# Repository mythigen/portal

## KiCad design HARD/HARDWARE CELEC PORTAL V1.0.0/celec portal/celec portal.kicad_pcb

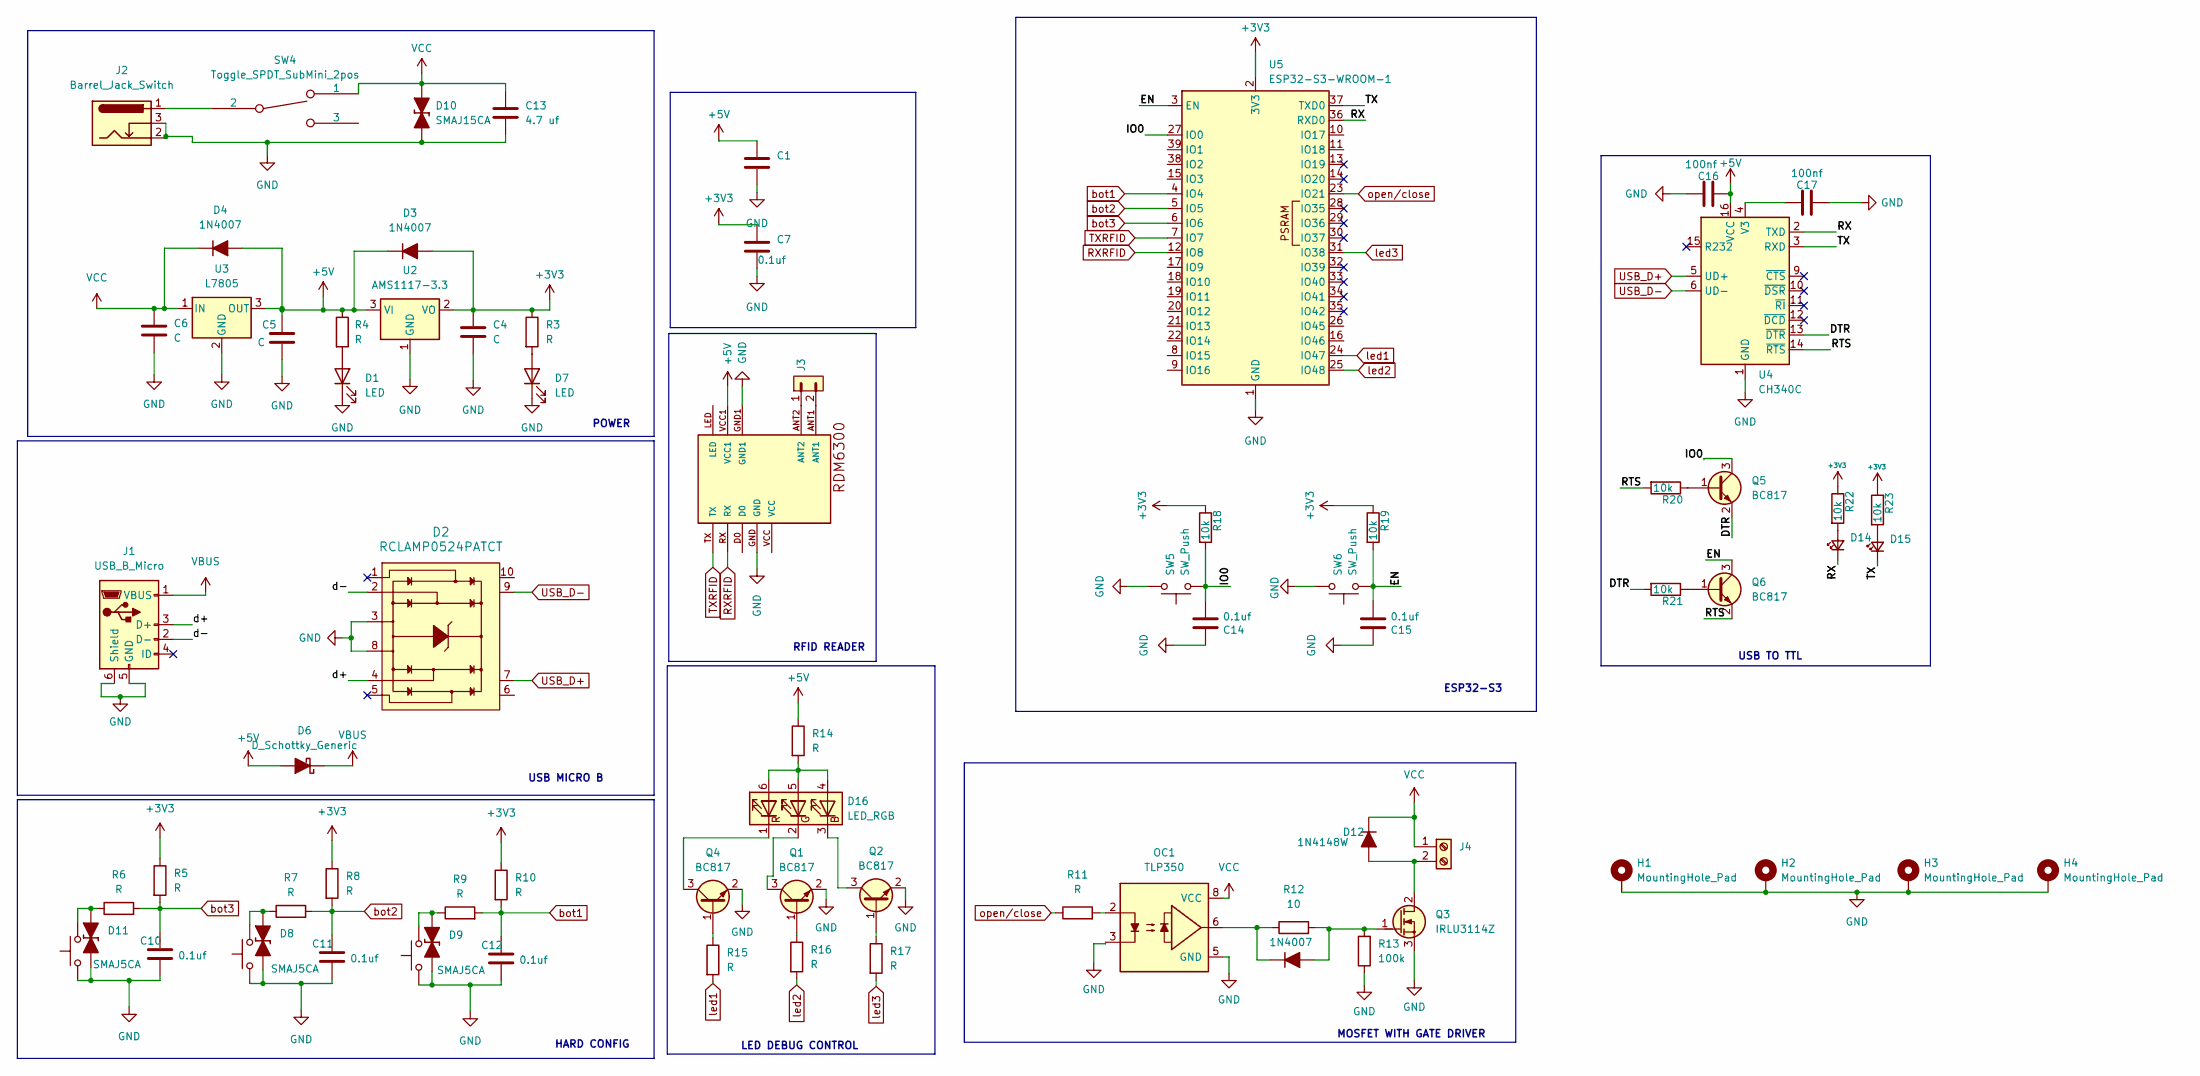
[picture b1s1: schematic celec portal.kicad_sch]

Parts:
C1, C7, C10, C11, C12, C14, C15: 0.1uf; C_0805_2012Metric
C4, C5, C6: C; C_0805_2012Metric
C13: 4.7 uf; C_Elec_4x5.4
C16, C17: 100nf; C_0805_2012Metric
D1, D7: LED; LED_0805_2012Metric
D2: RCLAMP0524PATCT; UFDFN-10_2.5x1mm; MPN RCLAMP0524PATCT; Digi-Key_PN RCLAMP0524PACT-ND
D3, D4, D5: 1N4007; D_DO-214AC_SMA
D6: D_Schottky_Generic; D_DO-214AC_SMA
D8, D9, D11: SMAJ5CA; D_DO-214AC_SMA
D10: SMAJ15CA; D_DO-214AC_SMA
D12: 1N4148W; D_DO-15_P3.81mm_Vertical_AnodeUp
D14, D15: LED_Small; LED_0805_2012Metric
D16: LED_RGB; LED_RGB_5050-6
H1, H2, H3, H4: MountingHole_Pad; MountingHole_3.2mm_M3_Pad_Via
J1: USB_B_Micro; USB_Micro-B_Molex-105017-0001
J2: Barrel_Jack_Switch; BarrelJack_Horizontal
J3: PINHD_1x2_Male; PinHeader_1x02_P2.54mm_Vertical
J4: Screw_Terminal_01x02; TerminalBlock_bornier-2_P5.08mm
OC1: TLP350; DIP-8_W7.62mm
Q1, Q2, Q4, Q5, Q6: BC817; SOT-23
Q3: IRLU3114Z; TO-252-2
R3, R4, R5, R6, R7, R8, R9, R10, R11, R14, R15, R16, R17: R; R_0805_2012Metric
R12: 10; R_0805_2012Metric
R13: 100k; R_0805_2012Metric
R18, R19, R20, R21, R22, R23: 10k; R_0805_2012Metric
RDM1: RDM6300
SW1, SW2, SW3, SW5, SW6: SW_Push; SW_Tactile_SPST_NO_Straight_CK_PTS636Sx25SMTRLFS
SW4: Toggle_SPDT_SubMini_2pos; Switch_Toggle_SPDT_Mini_SolderLug; Part Number 200-MSP3-T2B3M2QE
U2: AMS1117-3.3; SOT-223-3_TabPin2
U3: L7805; TO-252-2
U4: CH340C; SOIC-16_3.9x9.9mm_P1.27mm
U5: ESP32-S3-WROOM-1

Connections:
+3V3: C4.1, C7.1, D3.2 (A), R3.1, R5.1, R8.1, R10.1, R18.1, R19.1, R22.1, R23.1, U2.2 (VO), U5.2 (3V3)
+5V: C1.1, C5.1, C16.2, D3.1 (K), D4.2 (A), D6.2 (A), R4.1, R14.1, RDM1.VCC1, U2.3 (VI), U3.3 (OUT), U4.16 (VCC); also elsewhere on the board
/DTR: Q5.2 (E), R21.2, U4.13 (~DTR)
/EN: C15.2, Q6.3 (C), R19.2, SW6.1, U5.3 (EN)
/IO0: C14.2, Q5.3 (C), R18.2, SW5.1, U5.27 (IO0)
/RTS: Q6.2 (E), R20.2, U4.14 (~RTS)
/RX: D14.1 (K), U4.2 (TXD), U5.36 (RXD0)
/TX: D15.1 (K), U4.3 (RXD), U5.37 (TXD0)
/d+: D2.4, J1.3 (D+)
/d-: D2.2, J1.2 (D-)
GND: C1.2, C4.2, C5.2, C6.2, C7.2, C10.2, C11.2, C12.2, C13.2, C14.1, C15.1, C16.1, C17.2, D1.1 (K), D2.3, D2.8, D7.1 (K), D8.1 (K), D9.1 (K), D10.1 (K), D11.1 (K), H1.1, H2.1, H3.1, H4.1, J1.5 (GND), J1.6 (Shield), J2.2, J2.3, OC1.3, OC1.5 (GND), Q1.2 (E), Q2.2 (E), Q3.3 (S), Q4.2 (E), R13.1, RDM1.GND, RDM1.GND1, SW1.1, SW2.1, SW3.1, SW5.2, SW6.2, U2.1 (GND), U3.2 (GND), U4.1 (GND), U5.1 (GND), U5.40 (GND), U5.41 (GND); also elsewhere on the board
unnamed: D1.2 (A), R4.2
unnamed: D5.2 (A), Q3.1 (G), R12.2, R13.2
unnamed: D5.1 (K), OC1.6, R12.1
unnamed: D7.2 (A), R3.2
unnamed: D8.2 (A), R7.1, SW2.2
unnamed: D9.2 (A), R9.1, SW3.2
unnamed: D11.2 (A), R6.1, SW1.2
unnamed: D12.2 (A), J4.2, Q3.2 (D)
unnamed: D14.2 (A), R22.2
unnamed: D15.2 (A), R23.2
unnamed: D16.4 (BA), D16.5 (GA), D16.6 (RA), R14.2
unnamed: D16.3 (BK), Q2.3 (C)
unnamed: D16.2 (GK), Q1.3 (C)
unnamed: D16.1 (RK), Q4.3 (C)
unnamed: J2.1, SW4.2
unnamed: J3.1, RDM1.ANT2
unnamed: J3.2, RDM1.ANT1
unnamed: OC1.2, R11.2
unnamed: Q1.1 (B), R16.1
unnamed: Q2.1 (B), R17.1
unnamed: Q4.1 (B), R15.1
unnamed: Q5.1 (B), R20.1
unnamed: Q6.1 (B), R21.1
unnamed: C17.1, U4.4 (V3)
RXRFID: RDM1.RX, U5.12 (IO8)
TXRFID: RDM1.TX, U5.7 (IO7)
USB_D+: D2.7, U4.5 (UD+)
USB_D-: D2.9, U4.6 (UD-)
VBUS: D6.1 (K), J1.1 (VBUS)
VCC: C6.1, C13.1, D4.1 (K), D10.2 (A), D12.1 (K), J4.1, OC1.8 (VCC), SW4.1, U3.1 (IN)
bot1: C12.1, R9.2, R10.2, U5.4 (IO4)
bot2: C11.1, R7.2, R8.2, U5.5 (IO5)
bot3: C10.1, R5.2, R6.2, U5.6 (IO6)
led1: R15.2, U5.24 (IO47)
led2: R16.2, U5.25 (IO48)
led3: R17.2, U5.31 (IO38)
open/close: R11.1, U5.23 (IO21)

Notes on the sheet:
POWER
HARD CONFIG
USB MICRO B
MOSFET WITH GATE DRIVER
RFID READER
ESP32-S3
USB TO TTL
LED DEBUG CONTROL

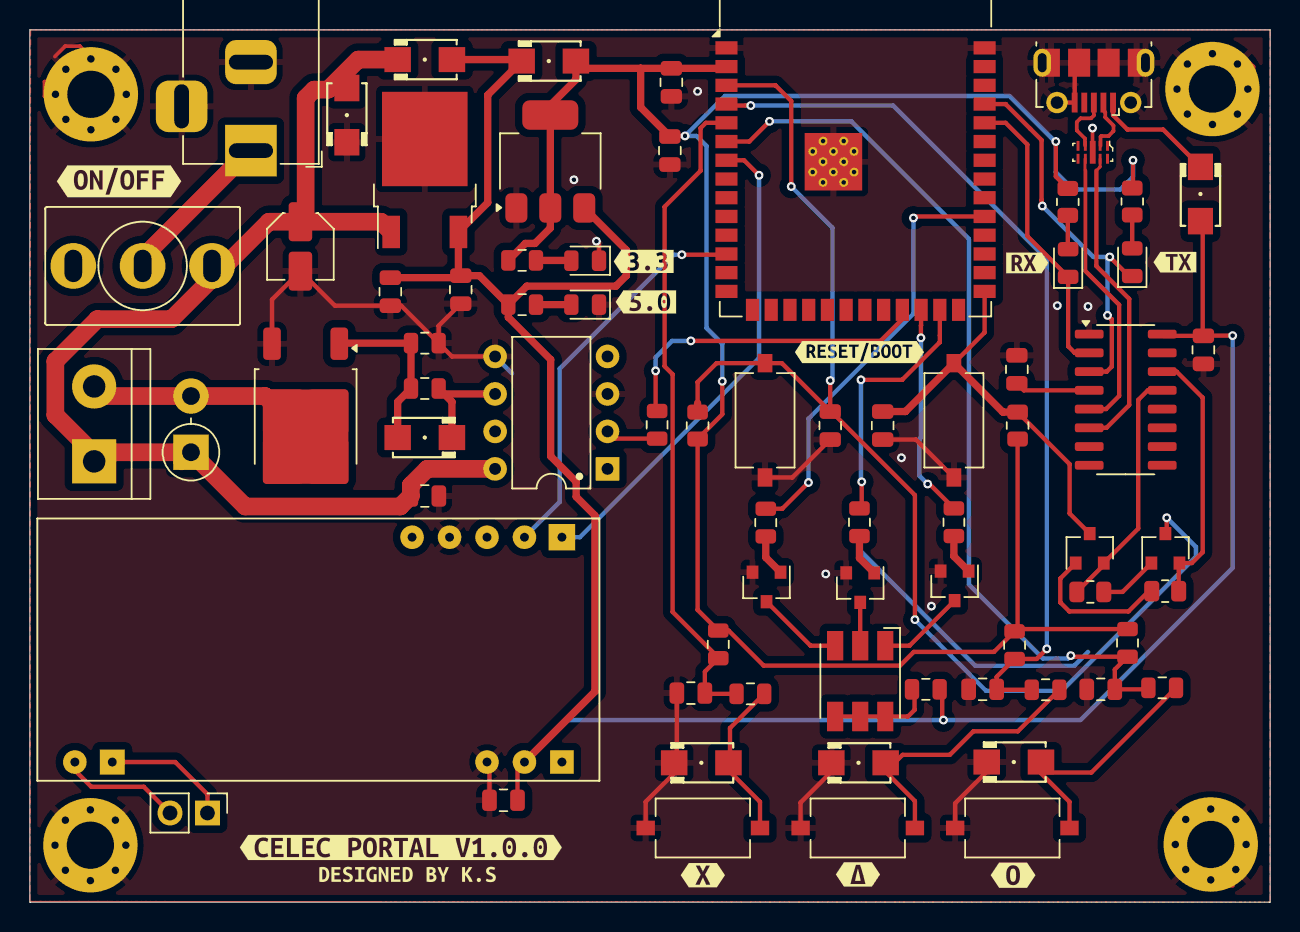
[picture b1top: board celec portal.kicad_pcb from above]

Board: 2 copper layers, 84.1 x 59.1 mm, 87 parts (0 on the bottom side), 48 nets.

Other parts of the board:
C3: 0.1uf; C_0805_2012Metric
kibuzzard-66BBE052: G***; kibuzzard-66BBE052
kibuzzard-66BBE129: G***; kibuzzard-66BBE129
kibuzzard-66BBE167: G***; kibuzzard-66BBE167
kibuzzard-66BBEED0: G***; kibuzzard-66BBEED0
kibuzzard-66BBEF2E: G***; kibuzzard-66BBEF2E
kibuzzard-66BBEF08: G***; kibuzzard-66BBEF08
kibuzzard-66BBF1B2: G***; kibuzzard-66BBF1B2
kibuzzard-66BBF1BD: G***; kibuzzard-66BBF1BD
kibuzzard-66BBF090: G***; kibuzzard-66BBF090
kibuzzard-66BBFAF7: G***; kibuzzard-66BBFAF7
kibuzzard-66BC06DF: G***; kibuzzard-66BC06DF

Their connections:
+5V: C3.1; also elsewhere on the board
GND: C3.2; also elsewhere on the board

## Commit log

2024-07-29 configured web gui setup
2024-07-29 added unit testing
2024-07-29 Add files via upload
    lib
2024-07-29 Create esp
2024-08-07 updated structure
2024-08-14 Create HARDWARE
2024-08-14 Create HARDWAER
2024-08-15 Create HARD
2024-10-12 gradle and platformio setup with sveltekit
2024-10-13 [feat]: added migrations scripts
2024-10-16 initialized tasks and base files
2024-10-25 [feat] dashboard basic file structure
2024-10-25 [fix] moved headers to `include` directory
2024-10-25 [fix] stripping elf file after build
2024-10-25 [feat] document based data storage schemas
2024-10-25 [feat] http web server boilerplate
